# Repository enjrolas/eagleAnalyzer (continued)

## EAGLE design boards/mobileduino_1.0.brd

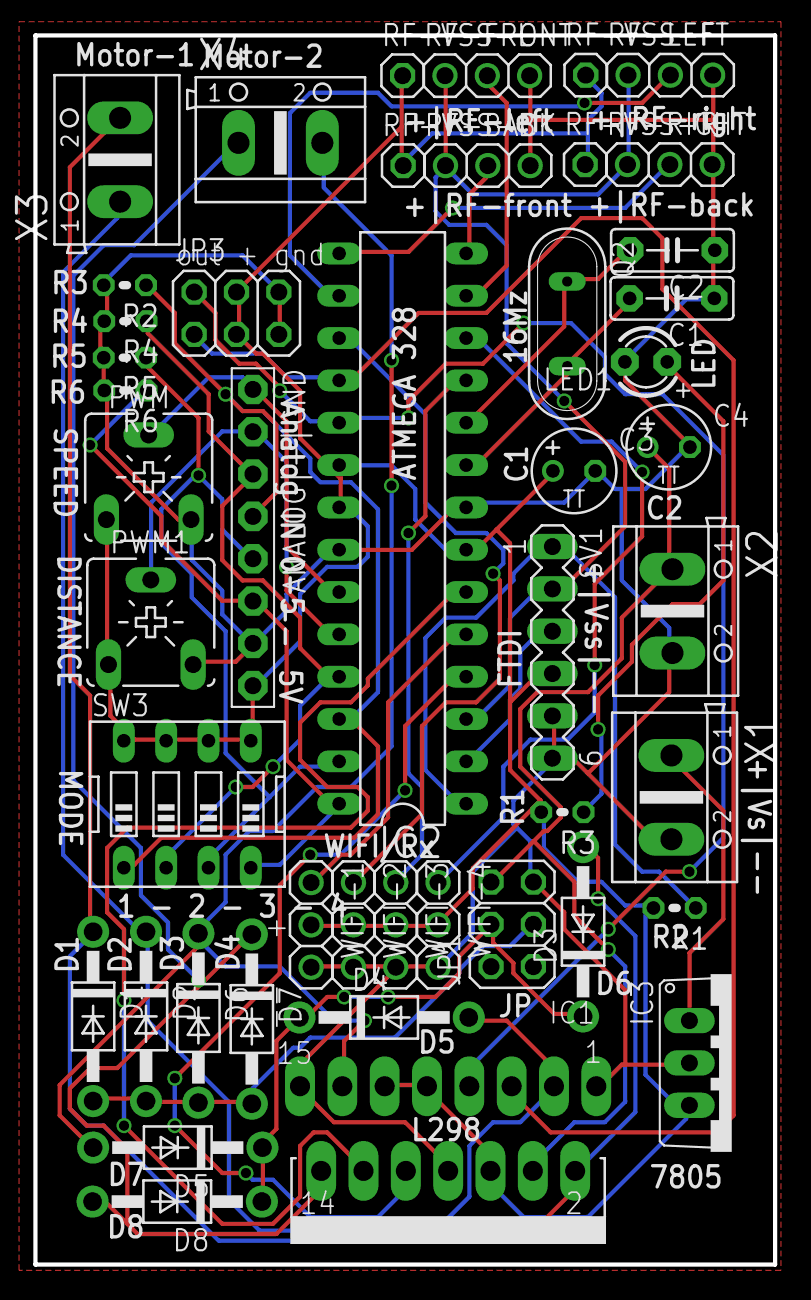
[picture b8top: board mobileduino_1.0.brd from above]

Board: 2 copper layers, 44.4 x 73.8 mm, 46 parts (0 on the bottom side), 34 nets.

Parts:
ANALOG|+|GND: 1X08-BIG
C1, C2: C5B2.5
C3, C4: TT2D5
D1, D2, D3, D4, D5, D6, D7, D8: 1N4004; DO41-10
IC1: L298; MULTIWATT-15
IC2: ATMEGA168V-10P; DIL28-3
IC3: 7805TV; TO220V
JP1, JP3: 2X03
LED1: LED3MM
PWM, PWM1: CA6V
Q2: QS
R1, R2, R3, R4, R5, R6: 0204V
RF-BACK: 1X03
RF-FRONT: 1X03
RF-LEFT: 1X03
RF-RIGHT: 1X03
RF-VSS-B: 1X01
RF-VSS-F: 1X01
RF-VSS-L: 1X01
RF-VSS-R: 1X01
SV1: MA06-1
SW3: EDG-04
WIFI-1, WIFI-2, WIFI-3, WIFI-4: 1X03
X1, X2, X3, X4: AK500/2

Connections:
unnamed: IC1.5, IC2.18, JP3.1
unnamed: D1.C, D3.A, IC1.2, X3.2
unnamed: D2.C, D4.A, IC1.3, X3.1
unnamed: D5.A, D6.C, IC1.13, X4.2
unnamed: D7.C, D8.A, IC1.14, X4.1
unnamed: C4.+, IC1.4, JP1.6, X2.1
unnamed: IC2.1, R1.1, SV1.1
unnamed: C1.2, IC2.9, Q2.2
unnamed: IC1.7, IC2.19, JP3.2
unnamed: C2.2, IC2.10, Q2.1
unnamed: IC3.1, X1.1
unnamed: IC2.16, RF-LEFT.2
unnamed: ANALOG|+|GND.1, IC2.23, PWM.S
unnamed: IC2.12, WIFI-4.1
unnamed: IC2.11, WIFI-3.1
unnamed: IC2.17, WIFI-2.1
unnamed: IC2.5, WIFI-1.1
unnamed: D3.C, D4.C, D5.C, D8.C, JP1.4
unnamed: IC1.10, IC2.4
unnamed: IC1.12, IC2.6
unnamed: IC2.15, RF-RIGHT.2
unnamed: ANALOG|+|GND.7, C1.1, C2.1, C3.-, C4.-, IC1.1, IC1.8, IC1.15, IC2.8, IC2.22, IC3.2, JP1.5, JP3.5, JP3.6, LED1.K, PWM.E, PWM1.E, R2.2, R4.2, R5.2, R6.2, RF-BACK.3, RF-FRONT.3, RF-LEFT.3, RF-RIGHT.3, SV1.5, SV1.6, WIFI-1.3, WIFI-2.3, WIFI-3.3, WIFI-4.3, X1.2, X2.2
unnamed: IC2.14, RF-BACK.2
unnamed: IC2.13, RF-FRONT.2
unnamed: IC2.3, RF-BACK.1, RF-FRONT.1, RF-LEFT.1, RF-RIGHT.1, SV1.2
unnamed: D1.A, D2.A, D6.A, D7.A, JP1.3
unnamed: ANALOG|+|GND.2, IC2.24, PWM1.S
unnamed: ANALOG|+|GND.3, IC2.25, R4.1, SW3.2
unnamed: ANALOG|+|GND.4, IC2.26, R2.1, SW3.1
unnamed: ANALOG|+|GND.5, IC2.27, R5.1, SW3.3
unnamed: IC2.2, SV1.3
unnamed: LED1.A, R3.1
unnamed: ANALOG|+|GND.6, IC2.28, R6.1, SW3.4
unnamed: ANALOG|+|GND.8, C3.+, IC1.6, IC1.9, IC1.11, IC2.7, IC2.20, IC2.21, IC3.3, JP3.3, JP3.4, PWM.A, PWM1.A, R1.2, R3.2, RF-VSS-B.1, RF-VSS-F.1, RF-VSS-L.1, RF-VSS-R.1, SV1.4, SW3.5, SW3.6, SW3.7, SW3.8, WIFI-1.2, WIFI-2.2, WIFI-3.2, WIFI-4.2
